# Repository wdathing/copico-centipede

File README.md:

# copico-centipede
A Radio Shack / Tandy Color Computer ("Coco") wildcard peripheral cartridge, with an RP2350 processor and 46 usable GPIO lines, covering most of the Coco's expansion port bus.

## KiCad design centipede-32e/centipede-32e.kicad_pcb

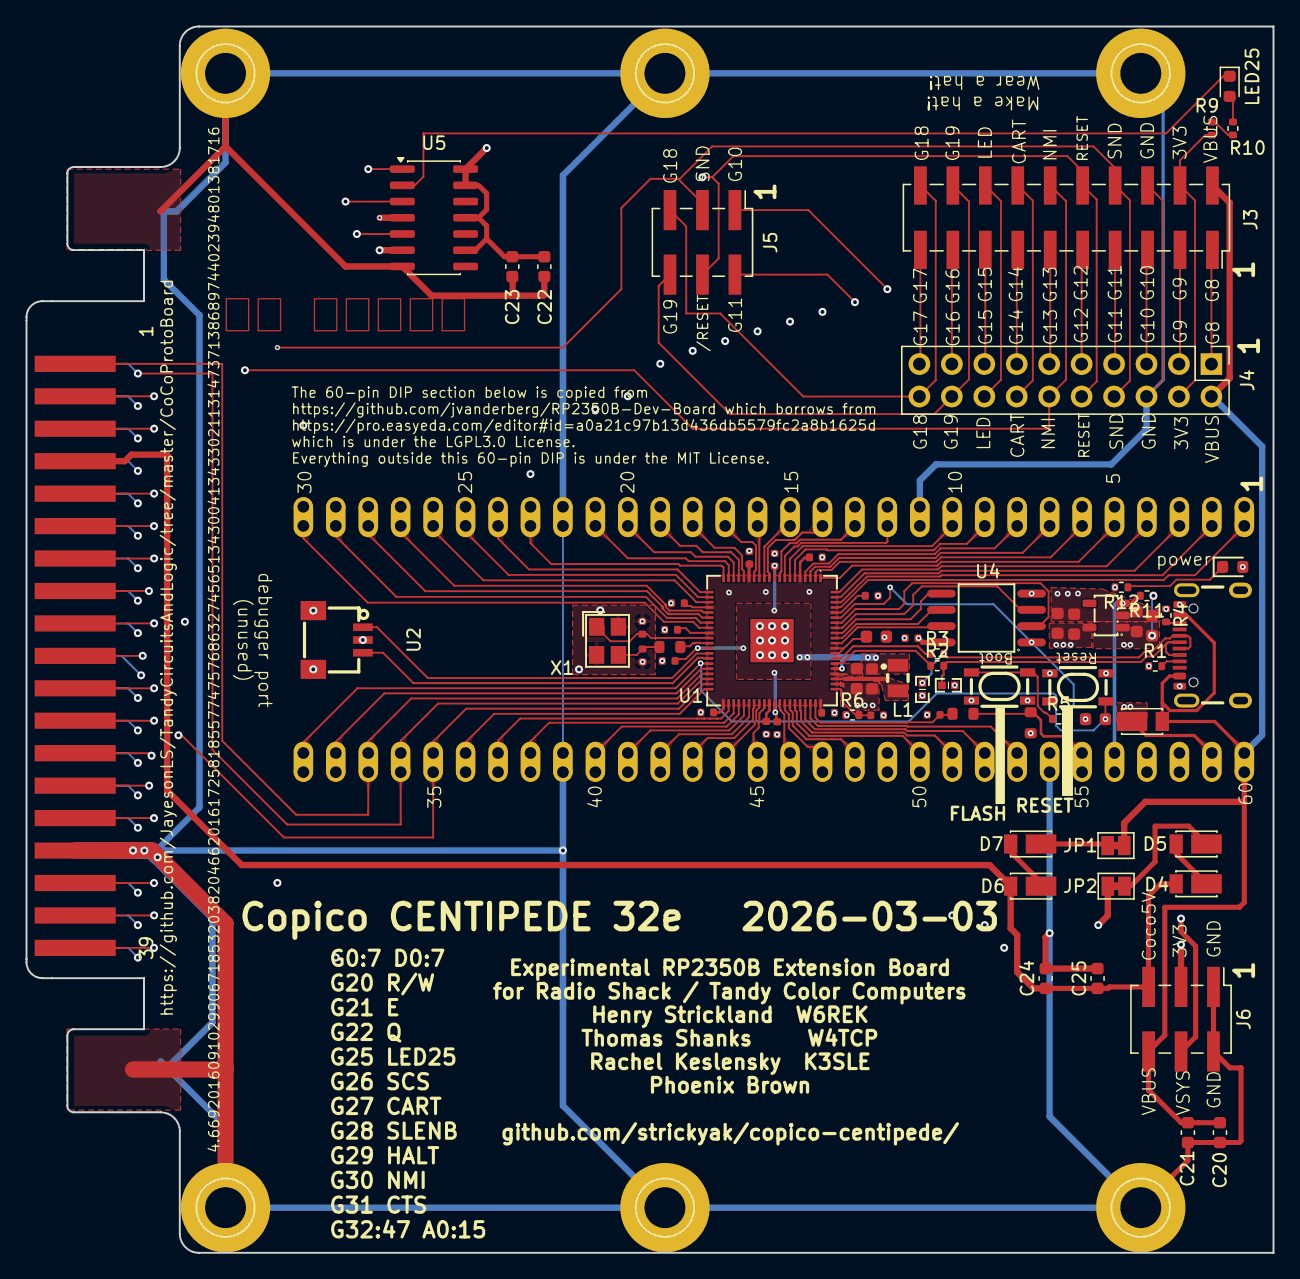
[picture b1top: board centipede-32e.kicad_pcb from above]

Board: 4 copper layers, 97.6 x 96.0 mm, 129 parts (0 on the bottom side), 90 nets.

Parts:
3V3_EN1, 3V31: Castellated Pad
ADC_VREF1: Castellated Pad
Boot1: K2-1808SN-A4SW-01; KEY-SMD_4P-L4.2-W3.2-P2.20-LS5.1-TL
C1, C2, C3, C4, C5, C6, C7, C8, C13, C14, C16, C36: 100nF; C_0402
C9, C15, C38, C39: 100nF; C_0603
C10, C12: 4.7uF; C_0603
C11, C19: 4.7uF; C_0402
C17, C18: 15pF; C_0402
C20, C22, C24: 10uF; C_0603_1608Metric
C21, C23, C25: 100nF; C_0603_1608Metric
C37, C40: 10uF; C_0603
D1, D4, D5, D6, D7: POWERDI-123_L2.8-W1.8-LS3.7-RD
D2, D3: RCLAMP0521P.TCT-MS; D0402-BI
GND1, GND2, GND3, GND4, GND4#2, GND6: Castellated Pad
GPI10: Castellated Pad
GPIO0, GPIO1, GPIO1#2, GPIO1#3, GPIO1#4, GPIO1#5, GPIO1#6, GPIO1#7, GPIO1#8, GPIO2, GPIO3, GPIO4, GPIO5, GPIO7, GPIO8, GPIO11, GPIO12, GPIO13, GPIO15, GPIO16, GPIO17, GPIO18, GPIO19, GPIO21, GPIO21#2, GPIO22, GPIO24, GPIO25, GPIO26, GPIO27, GPIO28, GPIO29, GPIO30, GPIO32, GPIO34, GPIO35, GPIO36, GPIO37, GPIO38, GPIO39, GPIO40, GPIO41, GPIO42, GPIO43, GPIO44, GPIO45, GPIO46: Castellated Pad
J3: Conn_02x10_Odd_Even; PinSocket_2x10_P2.54mm_Vertical_SMD
J4: Conn_02x10_Odd_Even; PinHeader_2x10_P2.54mm_Vertical
J5, J6: Conn_02x03_Odd_Even; PinHeader_2x03_P2.54mm_Vertical_SMD
JP1, JP2: SolderJumper_2_Bridged; SolderJumper-2_P1.3mm_Bridged_Pad1.0x1.5mm
L1: IND-SMD_L2.0-W1.6_AOTA-B201610S3R3-101-T
LED25: Red; LED_0603_1608Metric
P1: CocoEdgeConnector; CocoCardEdgeCocoMIDI
PWR_LED1: Red; D_0603
R1, R4: 5.1kΩ; R_0402_1005Metric
R2, R3, R6: 33Ω; R_0402_1005Metric
R5: 1kΩ; R_0402_1005Metric
R7: 1Ω; R_0603
R8: 200Ω; R_0603
R9, R10, R12: 2kΩ; R_0402_1005Metric
R11: 100kΩ; R_0402_1005Metric
R28: 1kΩ; R_0603
RUN1: Castellated Pad
Reset1: K2-1808SN-A4SW-01; KEY-SMD_4P-L4.2-W3.2-P2.20-LS5.1-TL
U1: QFN-80_L10.0-W10.0-P0.40-TL-EP3.4
U2: HC-1.0-3PWT; CONN-SMD_SM03B-SRSS-TB-LF-SN-P
U3: SOT-23-5_L3.0-W1.7-P0.95-LS2.8-BR
U4: W25Q128; SOIC-8_L5.3-W5.3-P1.27-LS8.0-BL
U5: 74HC14; SOIC-14_3.9x8.7mm_P1.27mm
USB1: USB-C-SMD_TYPE-C-6PIN-2MD-073
VBUS1: Castellated Pad
VSYS1: Castellated Pad
X1: CRYSTAL-SMD_4P-L3.2-W2.5-BL

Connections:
1V1: C2.1, C5.1, C10.2, C13.2, L1.2, U1.10 (DVDD), U1.32 (DVDD), U1.51 (DVDD), U1.65 (VREG_FB)
3V3: 3V31.57, C1.1, C3.1, C4.1, C6.1, C7.1, C8.2, C9.2, C12.2, C14.2, C16.2, C22.1, C23.1, C36.2, C38.1, C40.1, J3.4, J4.4, J6.3, PWR_LED1.2, R6.1, R8.2, R9.2, U1.5 (IOVDD), U1.15 (IOVDD), U1.24 (IOVDD), U1.29 (IOVDD), U1.41 (IOVDD), U1.50 (IOVDD), U1.60 (IOVDD), U1.64 (VREG_VIN), U1.68 (USB_OTP_VDD), U1.69 (QSPI_IOVDD), U1.76 (IOVDD), U3.5 (VOUT), U4.8 (VCC), U5.9, U5.11, U5.13, U5.14 (VCC)
3V3_EN: 3V3_EN1.56, R11.2, U3.3 (CE)
/VREG_LX: L1.1, U1.63 (VREG_LX)
ADC_VREF: ADC_VREF1.55, R7.2, R8.1
Coco5V: C24.1, C25.1, D4.2, D6.2, J6.5, P1.9 (+5V)
Eclk: P1.6 (E), U5.3
GND: Boot1.3, Boot1.4, C1.2, C2.2, C3.2, C4.2, C5.2, C6.2, C7.2, C8.1, C9.1, C10.1, C11.1, C12.1, C13.1, C14.1, C15.1, C16.1, C17.2, C18.1, C19.2, C20.2, C21.2, C22.2, C23.2, C24.2, C25.2, C36.1, C37.2, C38.2, C39.2, C40.2, D2.1, D3.1, GND2.22, GND3.39, GND4.49, GND4#2.54, GND6.58, GPI10.11, J3.6, J4.6, J6.1, J6.2, P1.33 (GND), P1.34 (GND), R1.1, R4.1, R12.2, Reset1.3, Reset1.4, U1.62 (VREG_PGND), U1.81 (GND), U2.2, U2.4, U2.5, U3.2 (VSS), U4.4 (GND), U5.7 (GND), USB1.1 (GND), USB1.12 (GND), USB1.13 (SHELL), USB1.14 (SHELL), X1.2 (GND), X1.4 (GND)
GPIO0: GPIO0.1, P1.10 (D0), U1.77 (GPIO0)
GPIO1: GPIO1#2.2, P1.11 (D1), U1.78 (GPIO1)
GPIO2: GPIO2.3, P1.12 (D2), U1.79 (GPIO2)
GPIO3: GPIO3.4, P1.13 (D3), U1.80 (GPIO3)
GPIO4: GPIO4.5, P1.14 (D4), U1.1 (GPIO4)
GPIO5: GPIO5.6, P1.15 (D5), U1.2 (GPIO5)
GPIO6: GPIO1#8.7, P1.16 (D6), U1.3 (GPIO6)
GPIO7: GPIO7.8, P1.17 (D7), U1.4 (GPIO7)
GPIO8: GPIO8.9, J3.1, J4.1, U1.6 (GPIO8)
GPIO9: GPIO1#7.10, J3.3, J4.3, U1.7 (GPIO9)
GPIO10: GND1.12, J3.5, J4.5, J5.1, U1.8 (GPIO10)
GPIO11: GPIO11.13, J3.7, J4.7, J5.2, U1.9 (GPIO11)
GPIO12: GPIO12.14, J3.9, J4.9, U1.11 (GPIO12)
GPIO13: GPIO13.15, J3.11, J4.11, U1.12 (GPIO13)
GPIO14: GPIO1#6.16, J3.13, J4.13, U1.13 (GPIO14)
GPIO15: GPIO15.17, J3.15, J4.15, U1.14 (GPIO15)
GPIO16: GPIO16.18, J3.17, J4.17, U1.16 (GPIO16)
GPIO17: GPIO17.19, J3.19, J4.19, U1.17 (GPIO17)
GPIO18: GPIO18.20, J3.20, J4.20, J5.5, U1.18 (GPIO18)
GPIO19: GPIO19.21, J3.18, J4.18, J5.6, U1.19 (GPIO19)
GPIO20: GPIO21.23, P1.18 (R/~W), U1.20 (GPIO20)
GPIO21: GPIO21#2.24, U1.21 (GPIO21), U5.4
GPIO22: GPIO22.25, U1.22 (GPIO22), U5.6
GPIO23: GPIO1#5.26, U1.23 (GPIO23)
GPIO24: GPIO24.27, U1.25 (GPIO24)
GPIO25: GPIO25.28, J3.16, J4.16, U1.26 (GPIO25), U5.1
GPIO26: GPIO26.29, P1.36 (~SCS), U1.27 (GPIO26)
GPIO27: GPIO27.30, J3.14, J4.14, P1.8 (~CART), U1.28 (GPIO27)
GPIO28: GPIO28.31, P1.40 (~SLENB), U1.36 (GPIO28)
GPIO29: GPIO29.33, P1.3 (~HALT), U1.37 (GPIO29)
GPIO30: GPIO30.34, J3.12, J4.12, P1.4 (~NMI), U1.38 (GPIO30)
GPIO31: GPIO1#4.1, GPIO1#4.35, P1.32 (~CTS), U1.39 (GPIO31)
GPIO32: GPIO1.36, P1.19 (A0), U1.40 (GPIO32)
GPIO33: GPIO32.37, P1.20 (A1), U1.42 (GPIO33)
GPIO34: GPIO34.38, P1.21 (A2), U1.43 (GPIO34)
GPIO35: GPIO35.40, P1.22 (A3), U1.44 (GPIO35)
GPIO36: GPIO36.41, P1.23 (A4), U1.45 (GPIO36)
GPIO37: GPIO37.42, P1.24 (A5), U1.46 (GPIO37)
GPIO38: GPIO38.43, P1.25 (A6), U1.47 (GPIO38)
GPIO39: GPIO39.44, P1.26 (A7), U1.48 (GPIO39)
GPIO40/ADC0: GPIO40.45, P1.27 (A8), U1.49 (GPIO40_ADC0)
GPIO41/ADC1: GPIO41.46, P1.28 (A9), U1.52 (GPIO41_ADC1)
GPIO42/ADC2: GPIO42.47, P1.29 (A10), U1.53 (GPIO42_ADC2)
GPIO43/ADC3: GPIO43.48, P1.30 (A11), U1.54 (GPIO43_ADC3)
GPIO44/ADC4: GPIO44.50, P1.31 (A12), U1.55 (GPIO44_ADC4)
GPIO45/ADC5: GPIO45.51, P1.37 (A13), U1.56 (GPIO45_ADC5)
GPIO46/ADC6: GPIO46.52, P1.38 (A14), U1.57 (GPIO46_ADC6)
GPIO47/ADC7: GPIO1#3.53, P1.39 (A15), U1.58 (GPIO47_ADC7)
LED25a: LED25.1, U5.2
LED25b: LED25.2, R10.1
unnamed: Boot1.1, Boot1.2, R5.1
unnamed: C17.1, R28.1, X1.3
unnamed: D4.1, D5.2
unnamed: D6.1, D7.2
unnamed: D7.1, JP1.2 (B)
unnamed: D5.1, JP2.1 (A)
unnamed: PWR_LED1.1, R12.1
unnamed: R9.1, R10.2
unnamed: C19.1, R7.1, U1.59 (ADC_AVDD)
unnamed: U1.71 (QSPI_SCLK), U4.6 (CLK)
unnamed: U1.72 (QSPI_SD0), U4.5 (DI)
unnamed: U1.74 (QSPI_SD1), U4.2 (DO)
unnamed: U1.73 (QSPI_SD2), U4.3 (IO2)
unnamed: U1.70 (QSPI_SD3), U4.7 (IO3)
unnamed: R5.2, U1.75 (QSPI_SS), U4.1 (CS#)
unnamed: U1.33 (SWCLK), U2.1
unnamed: U1.34 (SWDIO), U2.3
unnamed: R2.1, U1.66 (USB_DM)
unnamed: R3.1, U1.67 (USB_DP)
unnamed: C11.2, R6.2, U1.61 (VREG_AVDD)
unnamed: C18.2, U1.30 (XIN), X1.1
unnamed: R28.2, U1.31 (XOUT)
unnamed: R1.2, USB1.4 (CC1)
unnamed: R4.2, USB1.10 (CC2)
Qclk: P1.7 (Q), U5.5
RUN: C15.2, RUN1.30, Reset1.1, U1.35 (RUN)
SND: J3.8, J4.8, J5.3, P1.35 (SND)
USB2_D+: D3.2, R3.2, USB1.6 (DP1), USB1.8 (DP2)
USB2_D-: D2.2, R2.2, USB1.5 (DN2), USB1.7 (DN1)
VBUS: C20.1, C21.1, D1.2, J3.2, J4.2, J6.6, JP1.1 (A), USB1.2 (VBUS), USB1.11 (VBUS), VBUS1.60
VSYS: C37.1, C39.1, D1.1, J6.4, JP2.2 (B), R11.1, U3.1 (VIN), VSYS1.59
nRESET: J3.10, J4.10, J5.4, P1.5 (~RESET)

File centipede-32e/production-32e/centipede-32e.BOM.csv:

Designator,Footprint,Quantity,Value,LCSC Part #
"BOOT1, RESET1",KEY-SMD_4P-L4.2-W3.2-P2.20-LS5.1-TL,2,K2-1808SN-A4SW-01,C92589
"C1, C13, C14, C16, C2, C36, C7, C8",C_0402,8,100nF,C1525
"C10, C12",C_0603,2,4.7uF,C19666
"C11, C19",C_0402,2,4.7uF,C23733
"C15, C38, C39, C9",C_0603,4,100nF,C14663
"C17, C18",C_0402,2,15pF,C1548
"C3, C4, C5, C6",C_0402,4,100nF,C1525
"C37, C40",C_0603,2,10uF,C19702
"C20, C22, C24",C_0603,3,10uF,C19702
"C21, C23, C25",C_0603,3,100nF,C14663
"D1, D4, D5, D6, D7",POWERDI-123_L2.8-W1.8-LS3.7-RD,5,"50A PowerDI-123 Schottky Diodes",C110493
"D2, D3",D0402-BI,2,RCLAMP0521P.TCT-MS,C3029033
J3,"Connector_PinSocket_2.54mm:PinSocket_2x10_P2.54mm_Vertical_SMD",1,"2.54mm 20P 2x10P 3A 5mm Brass Gold Square Hole Surface Mount,Vertical Top SMD",C42163138
J5,"Connector_PinHeader_2.54mm:PinHeader_2x03_P2.54mm_Vertical_SMD",1,"2.54mm 2x3P 3A 6P 6mm Black Brass Gold Pin Header Surface Mount,Vertical SMD,P=2.54mm Pin Headers",C32713283
J6,"Connector_PinHeader_2.54mm:PinHeader_2x03_P2.54mm_Vertical_SMD",1,"2.54mm 2x3P 3A 6P 6mm Black Brass Gold Pin Header Surface Mount,Vertical SMD,P=2.54mm Pin Headers",C32713283
L1,IND-SMD_L2.0-W1.6_AOTA-B201610S3R3-101-T,1,~,C42411119
"PWR_LED1, LED25",D_0603,2,Red,C2286
"R1, R4",R_0402,2,5.1kΩ,C25905
R11,R_0402,1,100kΩ,C25741
"R12, R9, R10",R_0402,3,2kΩ,C4109
"R2, R3, R6",R_0402,3,33Ω,C25105
R28,R_0603,1,1kΩ,C21190
R5,R_0402,1,1kΩ,C11702
R7,R_0603,1,1Ω,C22936
R8,R_0603,1,200Ω,C8218
U1,QFN-80_L10.0-W10.0-P0.40-TL-EP3.4,1,RP2350B,C42415655
U2,CONN-SMD_SM03B-SRSS-TB-LF-SN-P,1,HC-1.0-3PWT,C2845362
U3,SOT-23-5_L3.0-W1.7-P0.95-LS2.8-BR,1,Voltage Regulator,C427602
U4,SOIC-8_L5.3-W5.3-P1.27-LS8.0-BL,1,W25Q128,C97521
U5,SOIC-14,1,"SN74LVC14ADR",C133541
USB1,USB-C-SMD_TYPE-C-6PIN-2MD-073,1,~,C2765186
X1,CRYSTAL-SMD_4P-L3.2-W2.5-BL,1,~,C20625731

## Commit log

2026-03-20 centipede-32d, centipede-32e
2026-04-17 burnlist.sh not-poke-mon.txt
2026-04-17 tiny script
2026-04-19 centipede-32z
2026-04-23 talk1a
2026-04-23 italk
2026-04-23 talk...
2026-04-23 talk
2026-04-25 32z, 250 MHz.
2026-04-25 add tether/
2026-04-30 Add first dragon stuff

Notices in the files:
centipede-32e/centipede-32e.kicad_pcb:
which is under the LGPL3.0 License.
Everything outside this 60-pin DIP is under the MIT License.
